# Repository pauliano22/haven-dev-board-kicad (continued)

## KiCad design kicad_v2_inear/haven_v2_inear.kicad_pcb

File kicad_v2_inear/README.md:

# Haven v2 BTE in-ear unit: schematic

The small board in the in-ear unit: SPH0641 PDM mic (the primary mic; SELECT low = DMIC0) (bottom port, needs a hole through the
board), 100 nF decoupling, a 33 Ω series resistor on the mic's data line, six cable pads and two
speaker pads. Target outline about 6 × 6 mm, 2-layer, 0.6 mm.

The design notes, cable harness table and decisions are in `../kicad_v2_pod/README.md`. Both
schematics are generated by `tools/gen_v2_bte_schematic.py`.

For the 2-wire variant (pod mic only), leave the mic, C1 and R1 off, or skip this board and wire the speaker straight to cable W5/W6.

## Layout (`haven_v2_inear.kicad_pcb`)

Generated by `tools/gen_v2_inear_pcb.py`. The script places, routes, pours and fills, and writes the
design rules into the `.kicad_pro`. Results: DRC 0 violations, 0 unconnected, and schematic parity 0
(`kicad-cli pcb drc --schematic-parity --severity-all`).

- 6 × 6 mm, 2-layer, 0.6 mm, corner radius 0.8. The outline matches haven-hardware
  `mechanical_cad/v2_bte/board_inear_outline.dxf`. One board fits both ears.
- **Bottom (driver side):** U13 SPH0641LU4H-1. It is bottom-port (datasheet / DigiKey "Port
  Location: Bottom"), so its port sits on a plated 0.4 mm hole at the board centre. That hole is
  pad 3 (GND), added to the footprint and lined up with the shell's mic hole. The driver pads
  TP1/TP2 sit on the same face as the speaker.
- **Top (lateral side):** cable pads W1..W6, with C1 next to W1 and R1 in the DATA line. Nothing
  is placed within 1.4 mm of the port (`GASKET_KEEPOUT` rule area), so a 0.5 mm foam gasket can
  seal the board to the shell's mic hole.
- Rules (JLCPCB 2-layer standard): 0.15 mm tracks, 0.127 mm clearance, 0.3 / 0.55 mm vias,
  0.25 mm copper to edge. GND is poured on both layers.

Before ordering, check:
- The port hole and the paste on the four GND pads around it, against the Knowles land-pattern
  drawing. Solder must not flow into the port. If it might, trim the paste on the inner corners.
- The SPK and cable wire pads (0.8 mm) are for hand soldering 6-wire harness conductors under
  a microscope. Vias are in the pads, which is fine for hand soldering.

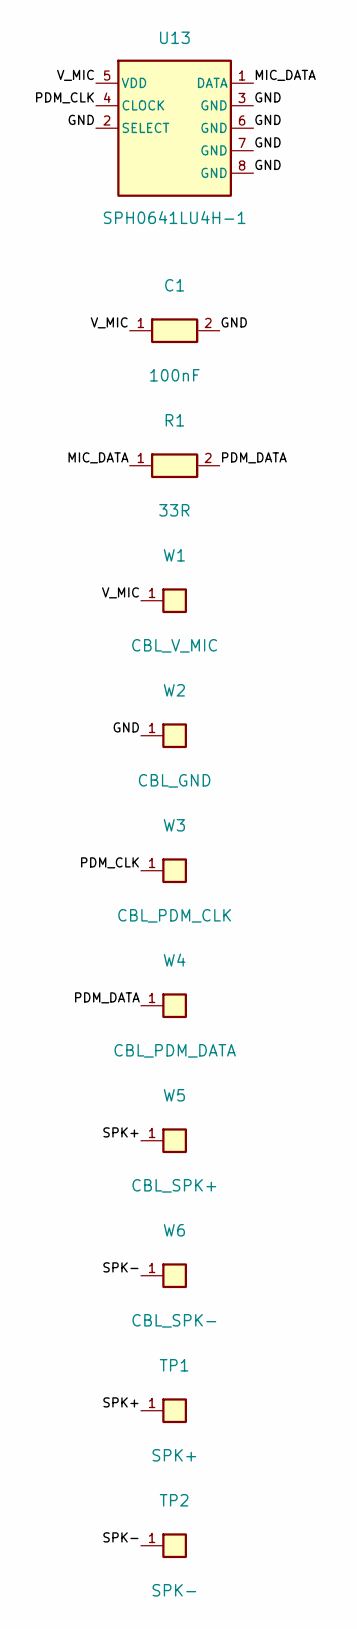
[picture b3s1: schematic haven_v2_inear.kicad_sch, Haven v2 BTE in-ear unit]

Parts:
C1: 100nF; C0201; MPN GRM033R60J104KE19D; LCSC C76928
R1: 33R; R0201; MPN ERJ1GNF33R0C; LCSC C717007
TP1: SPK+; Pad_1.2
TP2: SPK-; Pad_1.2
U13: SPH0641LU4H-1; MIC-SMD_5P_L3.5-W2.7-P0.82_SPH0641LU4H-1; MPN SPH0641LU4H-1; LCSC C2879853
W1: CBL_V_MIC; WirePad_0.8
W2: CBL_GND; WirePad_0.8
W3: CBL_PDM_CLK; WirePad_0.8
W4: CBL_PDM_DATA; WirePad_0.8
W5: CBL_SPK+; WirePad_0.8
W6: CBL_SPK-; WirePad_0.8

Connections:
/GND: C1.2, U13.2 (SELECT), U13.3 (GND), U13.6 (GND), U13.7 (GND), U13.8 (GND), W2.1
/MIC_DATA: R1.1, U13.1 (DATA)
/PDM_CLK: U13.4 (CLOCK), W3.1
/PDM_DATA: R1.2, W4.1
/SPK+: TP1.1, W5.1
/SPK-: TP2.1, W6.1
/V_MIC: C1.1, U13.5 (VDD), W1.1

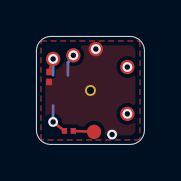
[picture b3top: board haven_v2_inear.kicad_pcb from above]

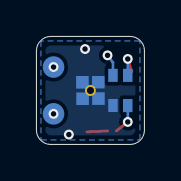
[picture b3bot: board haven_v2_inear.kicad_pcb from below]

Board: 2 copper layers, 6.0 x 6.0 mm, 11 parts (3 on the bottom side), 7 nets.

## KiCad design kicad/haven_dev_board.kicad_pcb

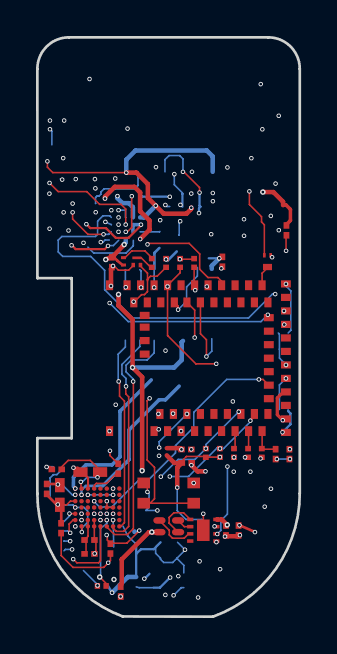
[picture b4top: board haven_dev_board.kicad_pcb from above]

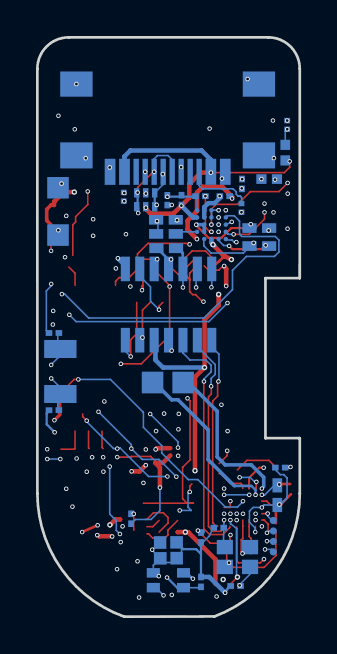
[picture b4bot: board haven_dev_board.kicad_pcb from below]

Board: 6 copper layers, 14.6 x 32.2 mm, 77 parts (39 on the bottom side), 61 nets.

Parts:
C1, C5, C7, C9, C10, C21, C29, C32, C36, C47: 1uF.1; C0201
C2, C14: 9pF.1; C0201
C3, C4: 4.7uF.1; C0201
C11, C12, C13, C27, C31, C38, C40, C42, C43, C44, C48: 100nF.1; C0201
C16, C20: 4.7uF, 10V.1; C0402
C17, C19, C22: 1uF >10V.1; C0201
C18: 10uF, >4V.1; C0402
C33, C34, C41: 10uF.1; C0402
C45, C46: GRM0335C1H330JA01D.1; b5c2858cad4e462ab76a8d0ccf4ade45
C49: C0402C103J3RACAUTO.1; cef4f92115b54348803d28f8706b0456
CRYSTAL1: CN4024M57620001.1; 6684822644394e4eba542a27714dd8a6
D2: PRTR5V0U2F.1; SON-6_L1.5-W1.0-P0.50-BL
J1: CLE-107-01-G-DV.1; CLE-107-01-X-DV
L2: 2.2uH.1; L0402
LED3: MHPA1010RGBDT.1; LED-ARRAY-SMD_4P-L1.0-W1.0-TR-RD
MDBT531: MDBT53.1; MDBT53
Q1: CSD23382F4.1; PICOSTAR-3_L1.0-W0.6-P0.35-TL
Q2: CSD13380F3T.1; PICOSTAR-3_L0.7-W0.6-P0.40-TL
R2, R3: 10kΩ.1; R0201
R4: 510Ω.1; R0201
R5, R9: 2kΩ.1; R0201
R6: 51kΩ.1; R0201
R7, R8: 5.1kΩ.1; R0201
R13: 37.4kΩ, 1%.1; R0402
R21: 0R; R0402
R23, R26: 27Ω.1; R0201
R27: 2.2Ω.1; R0201
R28: RC0201FR-07220RL.1; ea94e26560f84db4a6862024f5c3efa7
SW1: TS2819A 230GF.1; SW-SMD_4P-L2.8-W1.9-P1.16-LS3.0
TP_BAT+: pad; free_pad
TP_BAT-: pad; free_pad
TP_BCLK: pad; free_pad
TP_DIN: pad; free_pad
TP_DOUT: pad; free_pad
TP_LRCLK: pad; free_pad
TP_SPK+: pad; free_pad
TP_SPK-: pad; free_pad
U2: BQ25120AYFPR.1; DSBGA-25_L2.5-W2.6-R5-C5-P0.40-BL
U3: AP22916BCA4-7.1; X1-WLB0808-4_L0.8-W0.8-P0.40-TL
U4: XL-0201SURC.1; LED-SMD_L0.65-W0.35-P0.41_XL-0201SURC
U5: KTD2026.1; DFN-8_L1.5-W1.5-P0.40-BL-EP
U8: 1MΩ.1; R0201
U12: GT-USB-9047A.1; USB-C-SMD_GT-USB-9047A
U13: SPH0641LU4H-1.1; MIC-SMD_5P_L3.5-W2.7-P0.82_SPH0641LU4H-1
U15: ADAU1860BCBZRL.1; BGA-56_L3.0-W2.7-P0.35-R8-C7-TL
X1: Q13FC1350000200.1; FC-135R_L3.2-W1.5

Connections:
3V3: C5.2, C17.1, C29.2, C48.1, J1.10, LED3.1, U2.C5, U4.1, U5.5
#ERROR: MDBT531.3, Q2.1, U8.1
$1N48: R7.2, U12.A5
$1N49: R8.2, U12.B5
$1N65: C10.1, U2.C4
$1N98: C3.1, MDBT531.44, R27.2
$1N117: Q2.3, R4.2
$1N119: R4.1, U4.2
$1N151: C31.1, C36.1, U15.A3, U15.B3
$1N2586: C32.1, U15.G4
$1N16368: C45.1, CRYSTAL1.3, R28.1
+1.8V: C1.2, C4.2, C18.1, C20.2, J1.9, L2.2, MDBT531.38, MDBT531.41, Q1.2, R2.1, R3.1, U2.B5, U3.A2
BCLK: MDBT531.59, TP_BCLK.1, U15.B2
CC_#CD: MDBT531.26, U2.E2
CC_#PG: MDBT531.16, U2.D4
DAC_ENABLE: MDBT531.37, U15.E4
DAC_N: TP_SPK-.1, U15.G1
DAC_P: TP_SPK+.1, U15.F2
DIN: MDBT531.60, TP_DIN.1, U15.C1
DOUT: MDBT531.56, TP_DOUT.1, U15.B1
GND: C1.1, C2.1, C3.2, C4.1, C5.1, C7.2, C9.2, C10.2, C11.1, C12.1, C13.2, C14.1, C16.1, C17.2, C18.2, C19.2, C20.1, C21.1, C22.2, C27.1, C29.1, C31.2, C32.2, C33.1, C34.2, C36.2, C38.1, C40.2, C41.2, C42.1, C43.2, C44.2, C45.2, C46.1, C47.2, C48.2, C49.1, CRYSTAL1.2, CRYSTAL1.4, D2.2, J1.7, MDBT531.1, MDBT531.24, MDBT531.42, MDBT531.61, Q2.2, R6.1, R7.1, R8.1, SW1.3, SW1.4, TP_BAT-.1, U2.A1, U2.A5, U2.C1, U2.C2, U2.D1, U2.D5, U3.B1, U5.8, U5.9, U8.2, U12.12, U12.13, U12.14, U12.15, U12.A1B12, U12.A12B1, U13.2, U13.3, U13.6, U13.7, U13.8, U15.A1, U15.A4, U15.B4, U15.D6, U15.D7, U15.E6, U15.F1, U15.G3, U15.G7
INT: MDBT531.14, U2.D2
IO1: J1.11, MDBT531.9
IO2: J1.12, MDBT531.11
IO3: J1.14, MDBT531.13
LRCLK: MDBT531.57, TP_LRCLK.1, U15.C2
LSCTRL: MDBT531.27, U2.E3
MR#: Q1.1, SW1.1, SW1.2, U2.E1
ON+BTN: MDBT531.22, Q1.3
PDMCLK: U13.4, U15.C4
PDMDIN: U13.1, U15.C5
RESETN: C49.2, J1.5, MDBT531.6, U2.D3
RGB_B: LED3.4, U5.2
RGB_G: LED3.3, U5.3
RGB_R: LED3.2, U5.4
SCL: MDBT531.8, R3.2, U2.E5, U5.6
SCL1: MDBT531.45, R9.2, U15.C7
SDA: MDBT531.12, R2.2, U2.E4, U5.7
SDA1: MDBT531.47, R5.2, U15.C6
SENSORS_ENABLE: MDBT531.55, U3.B2
SW: L2.1, U2.A4
SWCLK: J1.1, MDBT531.2
SWDIO: J1.3, MDBT531.4
TCK: J1.8, U15.A5
TDI: J1.2, U15.A8
TDO: J1.4, U15.A7
TMS: J1.6, U15.A6
TS: R6.2, R13.1, U2.C3
USB_D+: MDBT531.46, R23.2
USB_D-: MDBT531.48, R26.2
USB_DM: D2.1, D2.6, R26.1, U12.A7, U12.B7
USB_DP: D2.3, D2.4, R23.1, U12.A6, U12.B6
VCC: C19.1, R21.2, U2.B1, U2.B2
VUSB: C22.1, D2.5, R13.2, R27.1, U2.A2, U12.A4B9, U12.A9B4
V_BAT: C21.2, R21.1, TP_BAT+.1
V_LS: C7.1, C11.2, C12.2, C13.1, C27.2, C33.2, C34.1, C38.2, C40.1, C41.1, C42.2, C43.1, C44.1, C47.1, J1.13, R5.1, R9.1, U3.A1, U13.5, U15.A2, U15.B5, U15.D1, U15.E1, U15.F3, U15.F7, U15.G2
V_PMID: C9.1, C16.2, U2.A3, U2.B3, U2.B4
XL1: C14.2, MDBT531.34, X1.1
XL2: C2.2, MDBT531.36, X1.2
XTALI: C46.2, CRYSTAL1.1, U15.B7
XTALO: R28.2, U15.B6

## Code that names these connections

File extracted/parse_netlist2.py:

#!/usr/bin/env python3
"""
Simpler, more robust net reconstruction: group real-component pins by the
nearest net-label instance (within SNAP radius), then group all pins whose
nearest label shares the same text -- since net-label text IS the net
identity in this kind of schematic, we don't need to trace wire topology.
Calibrated against a known-correct case (MDBT53 pin 60 / P0.28 <-> "DIN"
label, ~5 units apart) -- SNAP=25 gives comfortable margin.
"""
import json, math, re, html
from collections import defaultdict
from parse_symbol import parse_esym

def base_name_of(name):
    # Strip only a trailing ".<digits>" variant suffix (e.g. "5.1kΩ.1" -> "5.1kΩ"),
    # not a naive split on the first dot which mangles decimal values.
    return re.sub(r"\.\d+$", "", name or "")

SNAP = 25.0

# nRF5340 (MDBT53) dedicated DC-DC regulator / decoupling pins. Per the
# nRF5340 datasheet these connect ONLY to a local decoupling capacitor next
# to the pin, never to a routed signal net -- so proximity-based label
# matching produces false positives here (confirmed: DECR(58) picked up the
# neighboring LRCLK label, DCCD(50)/DECD(52) picked up FLASH_RESET/
# SD_ENABLE). Exclude by symbol pin name, not by (designator, pin number),
# so this stays correct if the schematic renumbers pins.
RESERVED_PIN_NAMES = {"DECR", "DCC", "DECD", "DCCD", "DCCH"}
BASE = "stock_openearable"
ESCH = f"{BASE}/SHEET/f608cfd613e24ea7937ea7eb0aab41a1/1.esch"

bom = json.load(open("bom.json"))
proj = json.load(open(f"{BASE}/project.json"))
symbol_title_to_uuid = {info["title"]: uid for uid, info in proj["symbols"].items()}
symbol_title_to_uuid_unescaped = {html.unescape(t): uid for t, uid in symbol_title_to_uuid.items()}

def rotate(x, y, rot):
    rot = (rot or 0) % 360
    if rot == 0: return x, y
    if rot == 90: return -y, x
    if rot == 180: return -x, -y
    if rot == 270: return y, -x
    rad = math.radians(rot)
    return x * math.cos(rad) - y * math.sin(rad), x * math.sin(rad) + y * math.cos(rad)

# 1. absolute pin positions for every real component
symcache = {}
pin_points = []  # (x, y, des, pinnum, pinname)
for des, c in bom.items():
    base_name = base_name_of(c["name"])
    uid = symbol_title_to_uuid.get(base_name) or symbol_title_to_uuid_unescaped.get(base_name)
    if not uid:
        print(f"WARN: no symbol found for {des} ({base_name})")
        continue
    if uid not in symcache:
        try:
            symcache[uid] = parse_esym(f"{BASE}/SYMBOL/{uid}.esym")
        except FileNotFoundError:
            symcache[uid] = {"pins": []}
    for p in symcache[uid]["pins"]:
        if p["name"] in RESERVED_PIN_NAMES:
            continue
        lx, ly = rotate(p["x"], p["y"], c["rot"] or 0)
        pin_points.append((c["x"] + lx, c["y"] + ly, des, p["number"], p["name"]))

# 2. net label instances
attrs_by_comp = defaultdict(dict)
comp_pos = {}
with open(ESCH) as f:
    for line in f:
        line = line.strip()
        if not line:
            continue
        d = json.loads(line)
        if d[0] == "COMPONENT":
            comp_pos[d[1]] = (d[3], d[4])
        elif d[0] == "ATTR" and len(d) > 4:
            attrs_by_comp[d[2]][d[3]] = d[4]

labels = []  # (x, y, name)
for cid, a in attrs_by_comp.items():
    nm = a.get("Name")
    des = a.get("Designator", "")
    fp = a.get("Footprint", "")
    if nm and not des and not fp and cid in comp_pos and "={" not in nm and "Anonymous" not in nm:
        x, y = comp_pos[cid]
        labels.append((x, y, nm))

print(f"{len(pin_points)} pin instances, {len(labels)} net-label instances")

# 3. for each pin, find nearest label within SNAP
def dist2(ax, ay, bx, by):
    return (ax - bx) ** 2 + (ay - by) ** 2

nets = defaultdict(list)
unmatched = []
for px, py, des, pinnum, pinname in pin_points:
    best = None
    bestd = SNAP * SNAP
    for lx, ly, nm in labels:
        d = dist2(px, py, lx, ly)
        if d <= bestd:
            bestd = d
            best = nm
    if best:
        nets[best].append((des, pinnum, pinname))
    else:
        unmatched.append((des, pinnum, pinname, px, py))

print(f"Pins matched to a named net: {sum(len(v) for v in nets.values())}")
print(f"Pins with no nearby label (unlabeled/direct-wire only): {len(unmatched)}")
print(f"Distinct net names: {len(nets)}")

out = {name: sorted(set((d, p) for d, p, _ in members)) for name, members in nets.items()}
json.dump(out, open("netlist.json", "w"), indent=1)
json.dump(
    [{"designator": d, "pin": p, "pin_name": pn, "x": x, "y": y} for d, p, pn, x, y in unmatched],
    open("unmatched_pins.json", "w"), indent=1,
)

print("\n=== nets with >=2 pins ===")
for name, members in sorted(out.items()):
    if len(members) >= 2:
        print(f"{name}: {members}")

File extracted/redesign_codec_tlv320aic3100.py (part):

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    established (TPS62822's regulated output) -- reused for the codec's
    DVDD, which needs 1.65-1.95V per its own datasheet. This only works
    because that redesign landed first.
  - DAC_N/DAC_P: ADAU1860's HPOUTN/HPOUTP were labeled with these but had
    only ONE owner each on this sheet (the chip itself) -- the real
    downstream receiver connection isn't modeled here, a pre-existing
    condition, not something this change creates or fixes. Preserved
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    whatever else might be on that chain.

Real, deliberate simplifications (each flagged, not hidden):
  - MCLK (pin 8) is tied to the same net as BCLK (pin 7) rather than
    adding a dedicated crystal -- TLV320AIC3100's own datasheet explicitly
    says "normally MCLK is PLL input; however, BCLK, GPIO1, etc. can also
    be PLL input," so the PLL is configured (in firmware/register init,
    not modeled here) to use BCLK as its reference instead. Avoids needing
    a new crystal for a part that didn't need its own oscillator before.
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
